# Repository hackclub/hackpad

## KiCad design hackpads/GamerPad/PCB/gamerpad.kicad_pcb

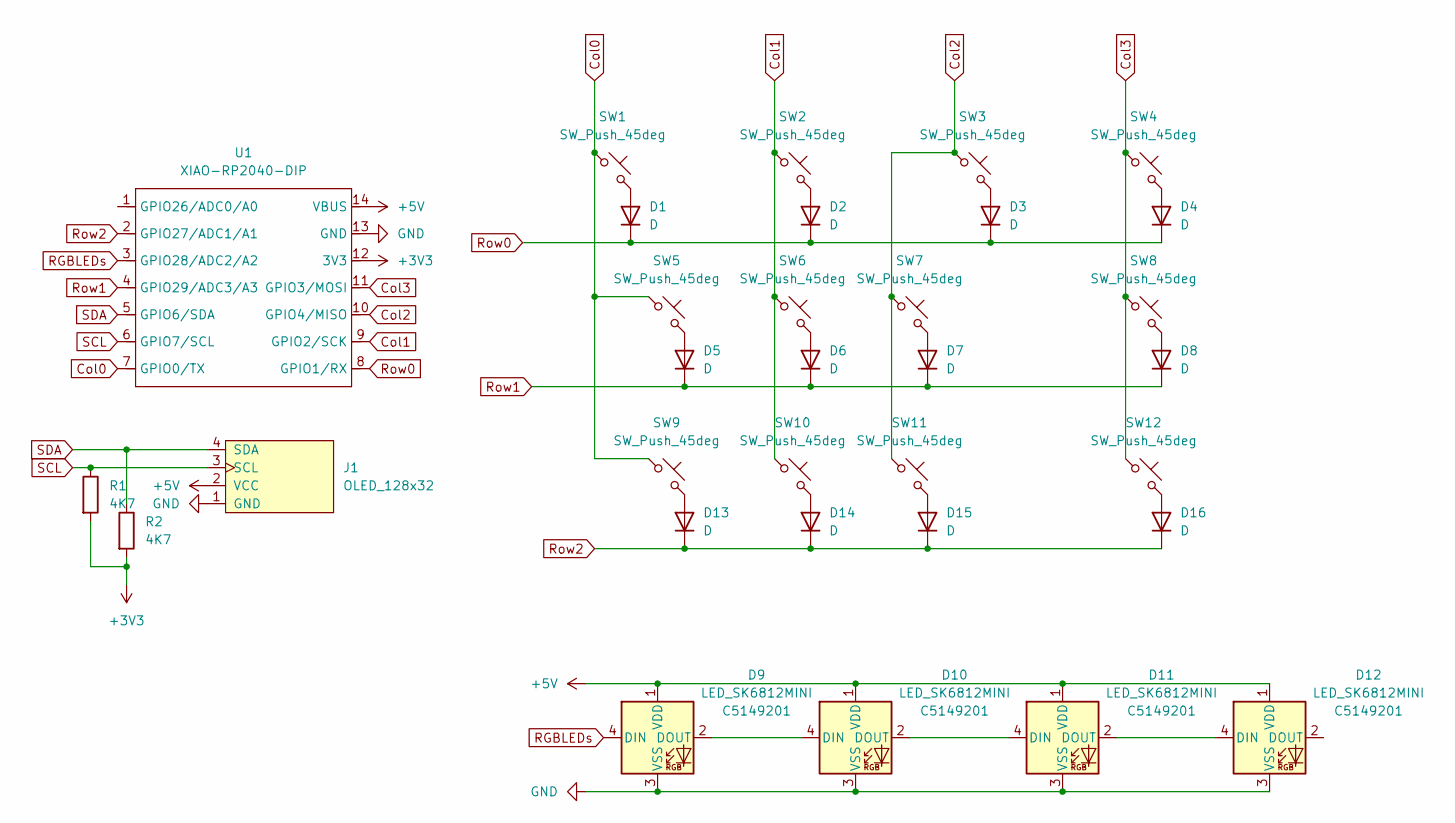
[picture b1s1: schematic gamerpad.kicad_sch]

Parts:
D1, D2, D3, D4, D5, D6, D7, D8, D13, D14, D15, D16: D; D_DO-35_SOD27_P7.62mm_Horizontal
D9, D10, D11, D12: LED_SK6812MINI; SK6812MINI-E; LCSC C5149201
J1: OLED_128x32
R1, R2: 4K7; R_Axial_DIN0204_L3.6mm_D1.6mm_P7.62mm_Horizontal
SW1, SW2, SW3, SW4, SW5, SW6, SW7, SW8, SW9, SW10, SW11, SW12: SW_Push_45deg; MX_PCB_1.00u
U1: XIAO-RP2040-DIP

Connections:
+3V3: R1.2, R2.2, U1.12 (3V3)
+5V: D9.1 (VDD), D10.1 (VDD), D11.1 (VDD), D12.1 (VDD), J1.2 (VCC), U1.14 (VBUS)
Col0: SW1.1, SW5.1, SW9.1, U1.7 (GPIO0/TX)
Col1: SW2.1, SW6.1, SW10.1, U1.9 (GPIO2/SCK)
Col2: SW3.1, SW7.1, SW11.1, U1.10 (GPIO4/MISO)
Col3: SW4.1, SW8.1, SW12.1, U1.11 (GPIO3/MOSI)
GND: D9.3 (VSS), D10.3 (VSS), D11.3 (VSS), D12.3 (VSS), J1.1 (GND), U1.13 (GND)
unnamed: D1.2 (A), SW1.2
unnamed: D2.2 (A), SW2.2
unnamed: D3.2 (A), SW3.2
unnamed: D4.2 (A), SW4.2
unnamed: D5.2 (A), SW5.2
unnamed: D6.2 (A), SW6.2
unnamed: D7.2 (A), SW7.2
unnamed: D8.2 (A), SW8.2
unnamed: D9.2 (DOUT), D10.4 (DIN)
unnamed: D10.2 (DOUT), D11.4 (DIN)
unnamed: D11.2 (DOUT), D12.4 (DIN)
unnamed: D13.2 (A), SW9.2
unnamed: D14.2 (A), SW10.2
unnamed: D15.2 (A), SW11.2
unnamed: D16.2 (A), SW12.2
RGBLEDs: D9.4 (DIN), U1.3 (GPIO28/ADC2/A2)
Row0: D1.1 (K), D2.1 (K), D3.1 (K), D4.1 (K), U1.8 (GPIO1/RX)
Row1: D5.1 (K), D6.1 (K), D7.1 (K), D8.1 (K), U1.4 (GPIO29/ADC3/A3)
Row2: D13.1 (K), D14.1 (K), D15.1 (K), D16.1 (K), U1.2 (GPIO27/ADC1/A1)
SCL: J1.3 (SCL), R1.1, U1.6 (GPIO7/SCL)
SDA: J1.4 (SDA), R2.1, U1.5 (GPIO6/SDA)

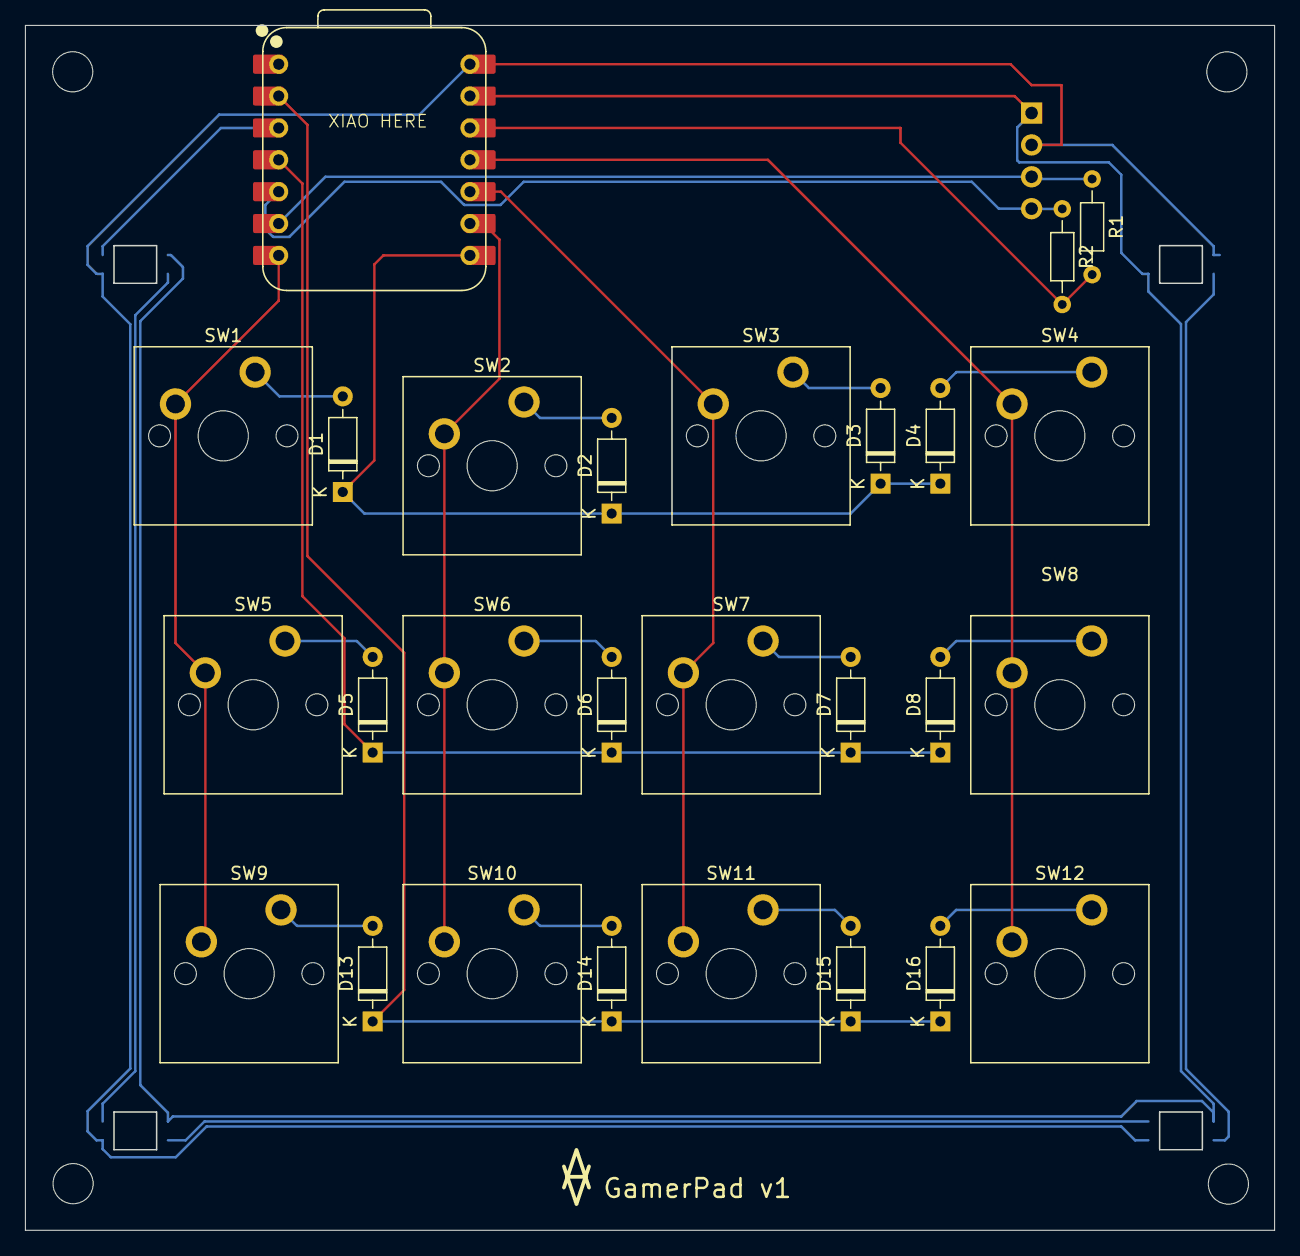
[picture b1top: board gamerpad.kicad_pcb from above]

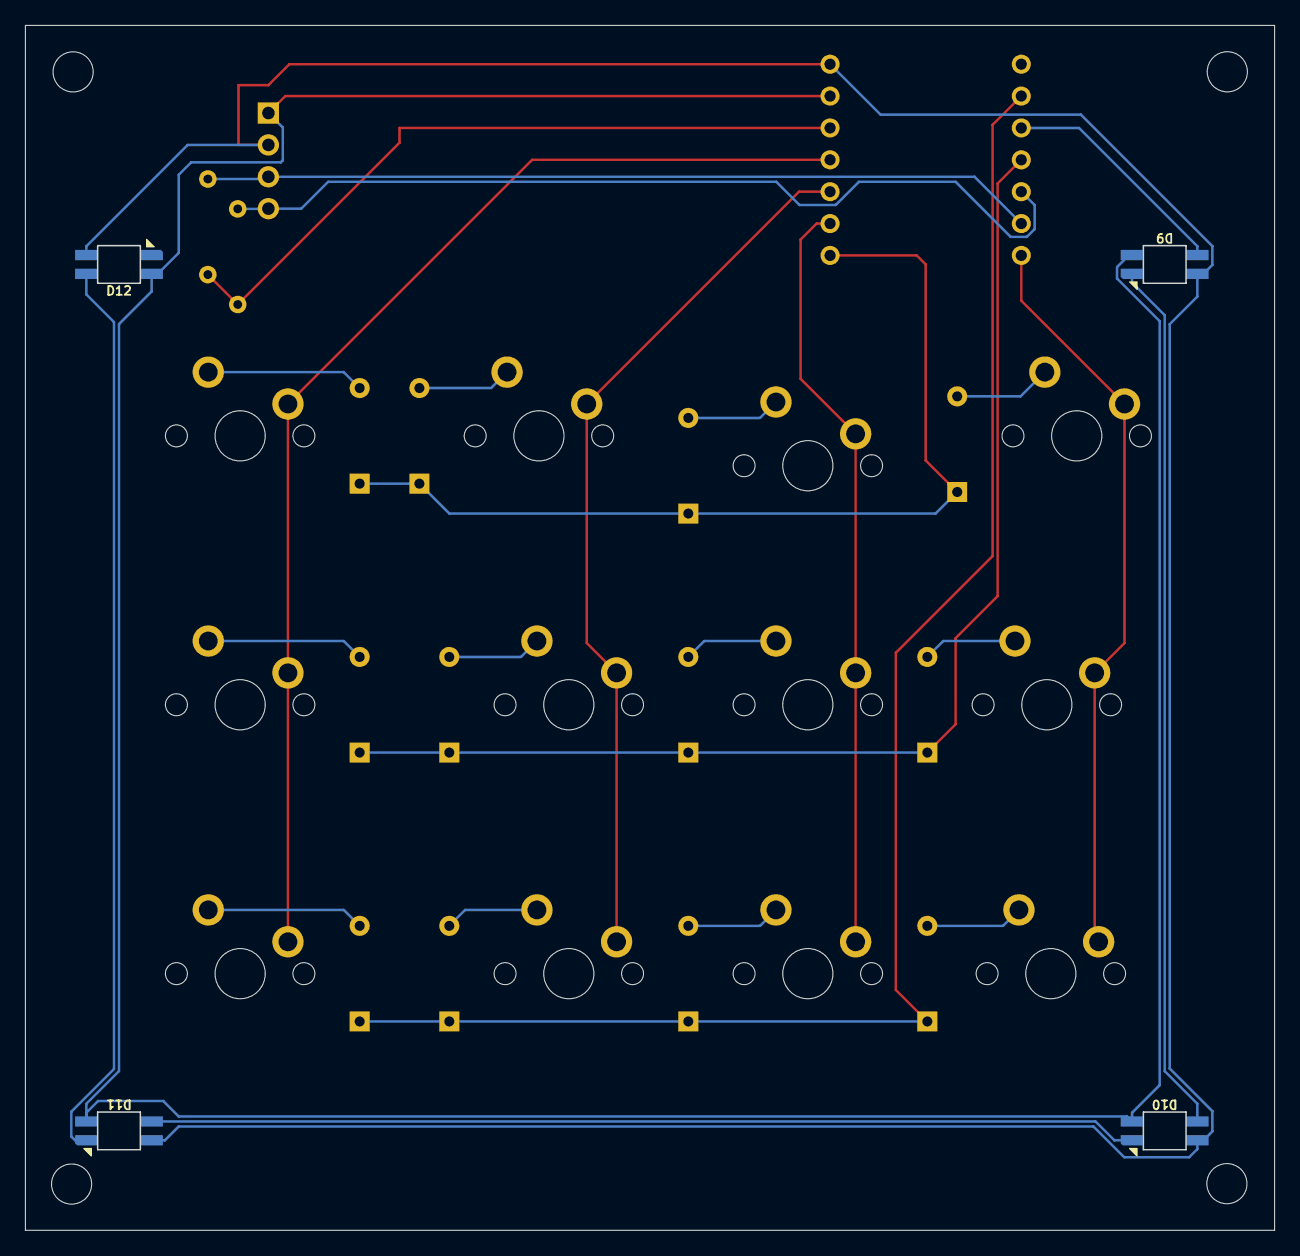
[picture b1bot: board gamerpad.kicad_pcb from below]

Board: 2 copper layers, 99.6 x 96.0 mm, 32 parts (4 on the bottom side), 28 nets.

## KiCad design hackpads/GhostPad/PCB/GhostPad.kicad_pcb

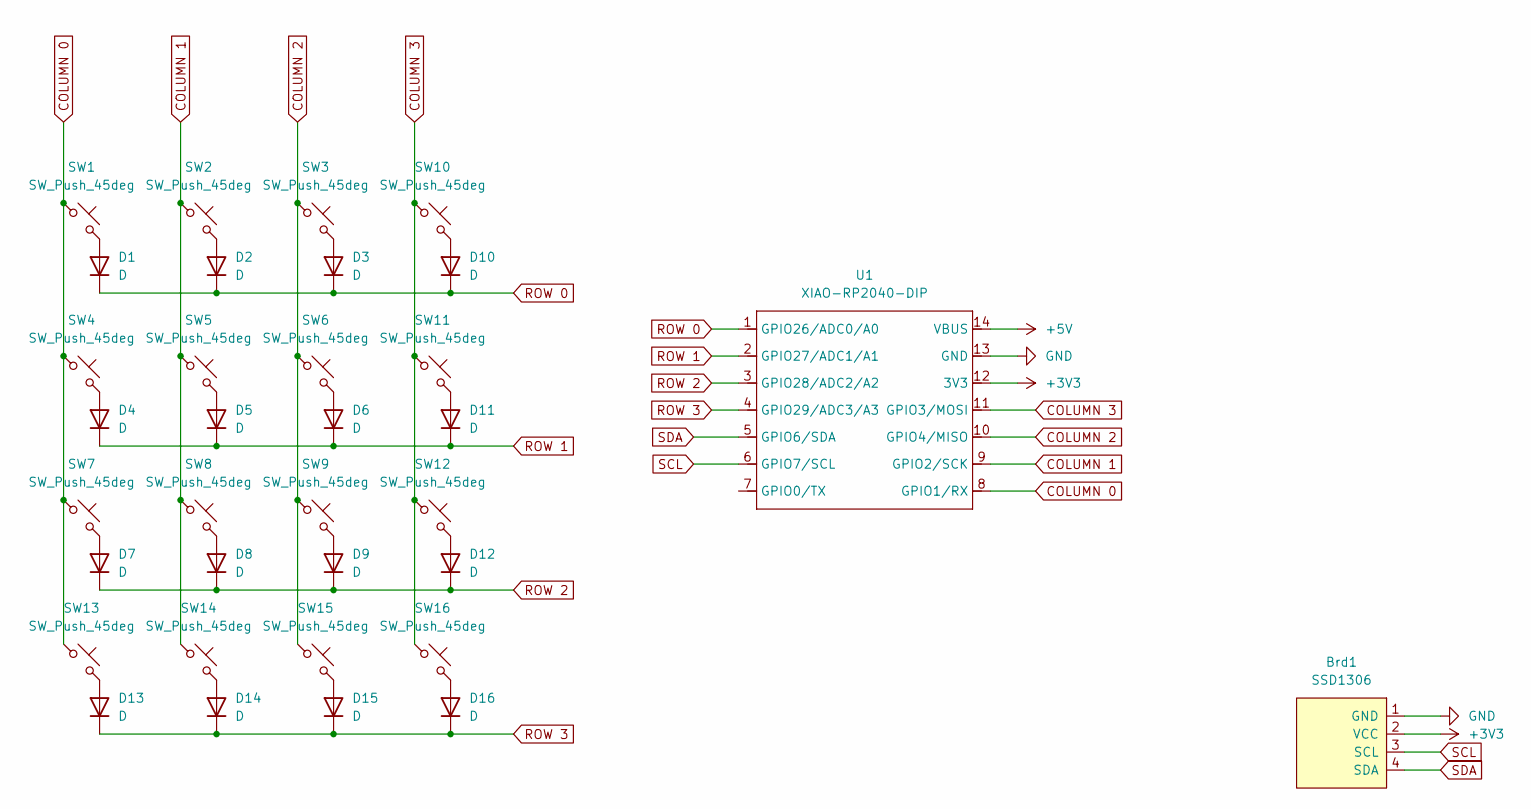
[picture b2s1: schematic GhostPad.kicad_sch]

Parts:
Brd1: SSD1306; 128x64OLED
D1, D2, D3, D4, D5, D6, D7, D8, D9, D10, D11, D12, D13, D14, D15, D16: D; D_0805_2012Metric_Pad1.15x1.40mm_HandSolder
SW1, SW2, SW3, SW4, SW5, SW6, SW7, SW8, SW9, SW10, SW11, SW12, SW13, SW14, SW15, SW16: SW_Push_45deg; SW_Cherry_MX_1.00u_PCB
U1: XIAO-RP2040-DIP

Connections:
+3V3: Brd1.2 (VCC), U1.12 (3V3)
+5V: U1.14 (VBUS)
COLUMN 0: SW1.1, SW4.1, SW7.1, SW13.1, U1.8 (GPIO1/RX)
COLUMN 1: SW2.1, SW5.1, SW8.1, SW14.1, U1.9 (GPIO2/SCK)
COLUMN 2: SW3.1, SW6.1, SW9.1, SW15.1, U1.10 (GPIO4/MISO)
COLUMN 3: SW10.1, SW11.1, SW12.1, SW16.1, U1.11 (GPIO3/MOSI)
GND: Brd1.1 (GND), U1.13 (GND)
unnamed: D1.2 (A), SW1.2
unnamed: D2.2 (A), SW2.2
unnamed: D3.2 (A), SW3.2
unnamed: D4.2 (A), SW4.2
unnamed: D5.2 (A), SW5.2
unnamed: D6.2 (A), SW6.2
unnamed: D7.2 (A), SW7.2
unnamed: D8.2 (A), SW8.2
unnamed: D9.2 (A), SW9.2
unnamed: D10.2 (A), SW10.2
unnamed: D11.2 (A), SW11.2
unnamed: D12.2 (A), SW12.2
unnamed: D13.2 (A), SW13.2
unnamed: D14.2 (A), SW14.2
unnamed: D15.2 (A), SW15.2
unnamed: D16.2 (A), SW16.2
ROW 0: D1.1 (K), D2.1 (K), D3.1 (K), D10.1 (K), U1.1 (GPIO26/ADC0/A0)
ROW 1: D4.1 (K), D5.1 (K), D6.1 (K), D11.1 (K), U1.2 (GPIO27/ADC1/A1)
ROW 2: D7.1 (K), D8.1 (K), D9.1 (K), D12.1 (K), U1.3 (GPIO28/ADC2/A2)
ROW 3: D13.1 (K), D14.1 (K), D15.1 (K), D16.1 (K), U1.4 (GPIO29/ADC3/A3)
SCL: Brd1.3 (SCL), U1.6 (GPIO7/SCL)
SDA: Brd1.4 (SDA), U1.5 (GPIO6/SDA)

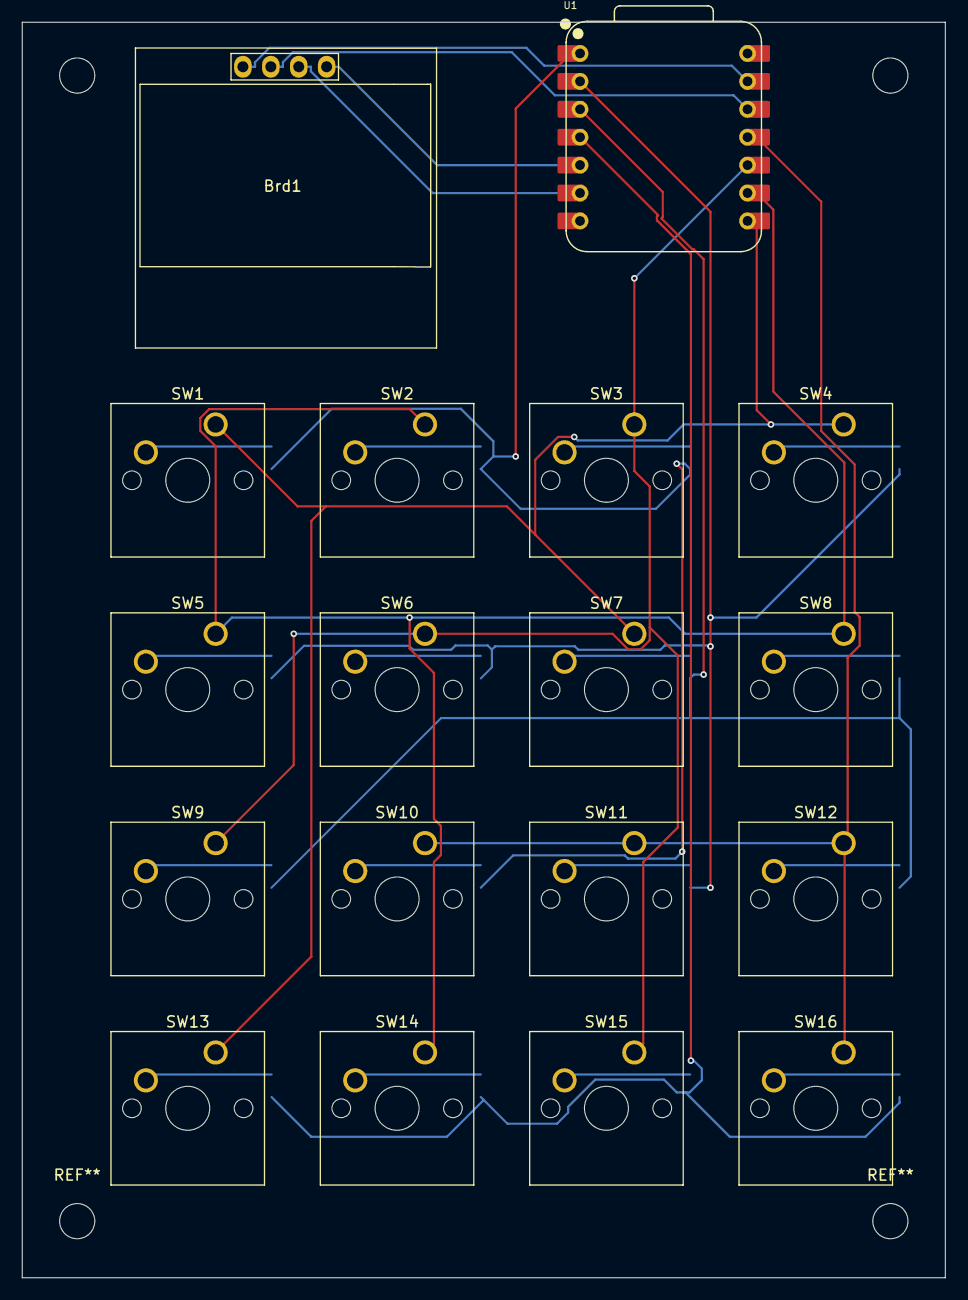
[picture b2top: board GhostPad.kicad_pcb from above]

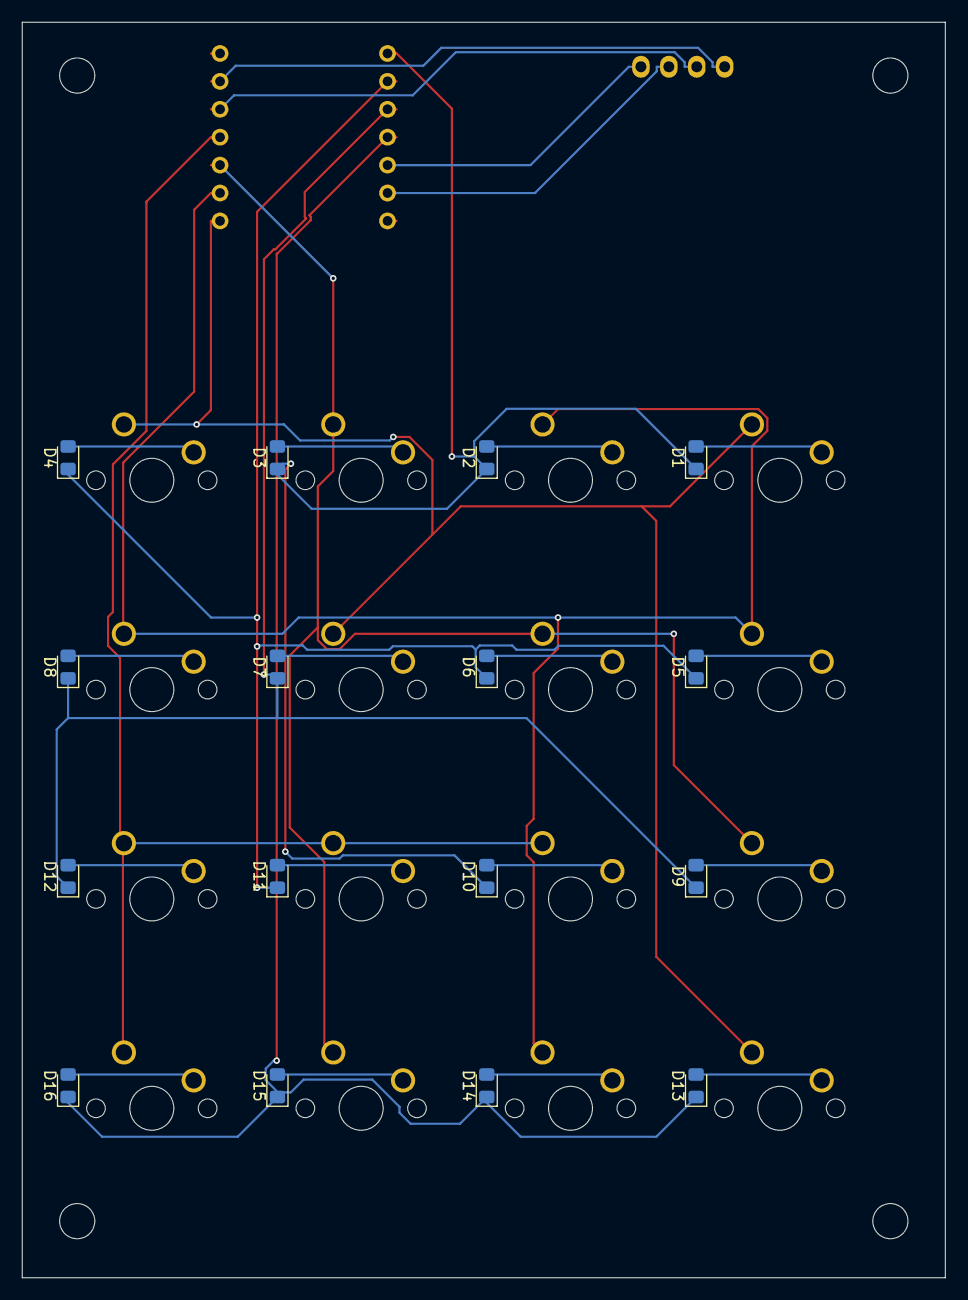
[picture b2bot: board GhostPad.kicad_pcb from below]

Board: 2 copper layers, 84.0 x 114.2 mm, 34 parts (16 on the bottom side), 28 nets.

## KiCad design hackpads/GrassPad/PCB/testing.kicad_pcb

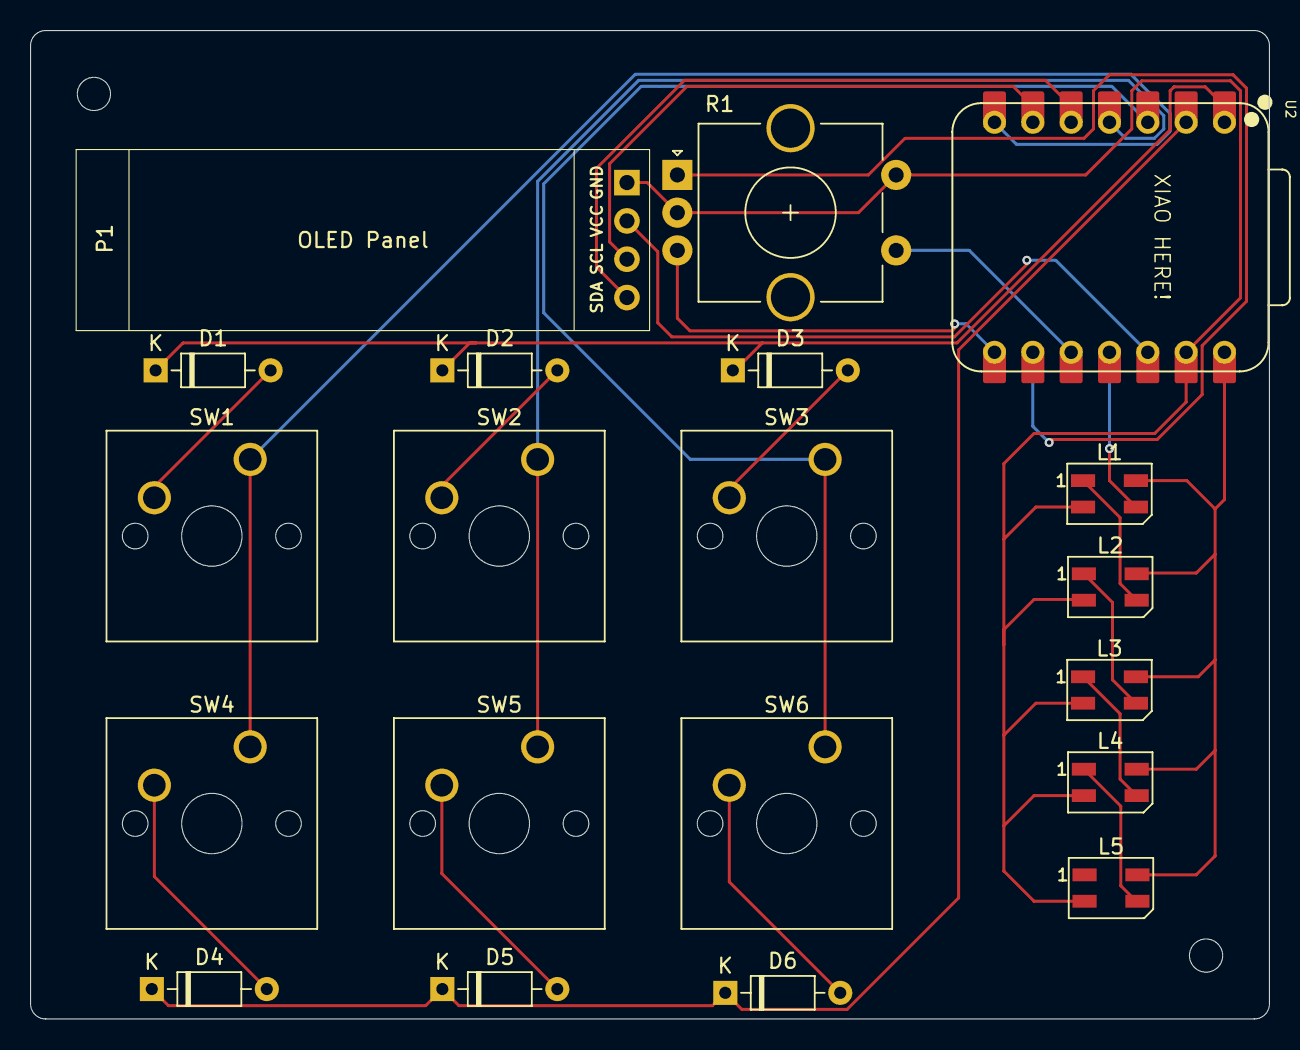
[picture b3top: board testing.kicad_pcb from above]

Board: 2 copper layers, 82.1 x 65.5 mm, 20 parts (0 on the bottom side), 24 nets.

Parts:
D1, D2, D3, D4, D5, D6: D; D_DO-35_SOD27_P7.62mm_Horizontal
L1, L2, L3, L4, L5: SK6812MINI; LED_SK6812MINI_PLCC4_3.5x3.5mm_P1.75mm
P1: Conn_01x04_Pin; SSD1306-0.91-OLED-4pin-128x32
R1: RotaryEncoder_Switch; RotaryEncoder_Alps_EC11E-Switch_Vertical_H20mm_CircularMoun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
SW1, SW2, SW3, SW4, SW5, SW6: SW_Push; SW_Cherry_MX_1.00u_PCB
U2: XIAO-RP2040-DIP

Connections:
+3.3V: P1.2, U2.12 (3V3)
+5V: L1.4 (VDD), L2.4 (VDD), L3.4 (VDD), L4.4 (VDD), L5.4 (VDD), U2.14 (VBUS)
GND: L1.2 (VSS), L2.2 (VSS), L3.2 (VSS), L4.2 (VSS), L5.2 (VSS), P1.1, R1.C, R1.S2, U2.13 (GND)
unnamed: L1.3 (DIN), U2.11 (GPIO3/MOSI)
unnamed: L1.1 (DOUT), L2.3 (DIN)
unnamed: L2.1 (DOUT), L3.3 (DIN)
unnamed: L3.1 (DOUT), L4.3 (DIN)
unnamed: L4.1 (DOUT), L5.3 (DIN)
unnamed: D1.2 (A), SW1.2
unnamed: D1.1 (K), D2.1 (K), D3.1 (K), U2.1 (GPIO26/ADC0/A0)
unnamed: D4.2 (A), SW4.2
unnamed: D4.1 (K), D5.1 (K), D6.1 (K), U2.2 (GPIO27/ADC1/A1)
unnamed: D5.2 (A), SW5.2
unnamed: D2.2 (A), SW2.2
unnamed: D3.2 (A), SW3.2
unnamed: D6.2 (A), SW6.2
unnamed: P1.3, U2.6 (GPIO7/SCL)
unnamed: P1.4, U2.5 (GPIO6/SDA)
unnamed: SW1.1, SW4.1, U2.7 (GPIO0/TX)
unnamed: R1.B, U2.8 (GPIO1/RX)
unnamed: R1.A, U2.9 (GPIO2/SCK)
unnamed: R1.S1, U2.10 (GPIO4/MISO)
unnamed: SW3.1, SW6.1, U2.3 (GPIO28/ADC2/A2)
unnamed: SW2.1, SW5.1, U2.4 (GPIO29/ADC3/A3)

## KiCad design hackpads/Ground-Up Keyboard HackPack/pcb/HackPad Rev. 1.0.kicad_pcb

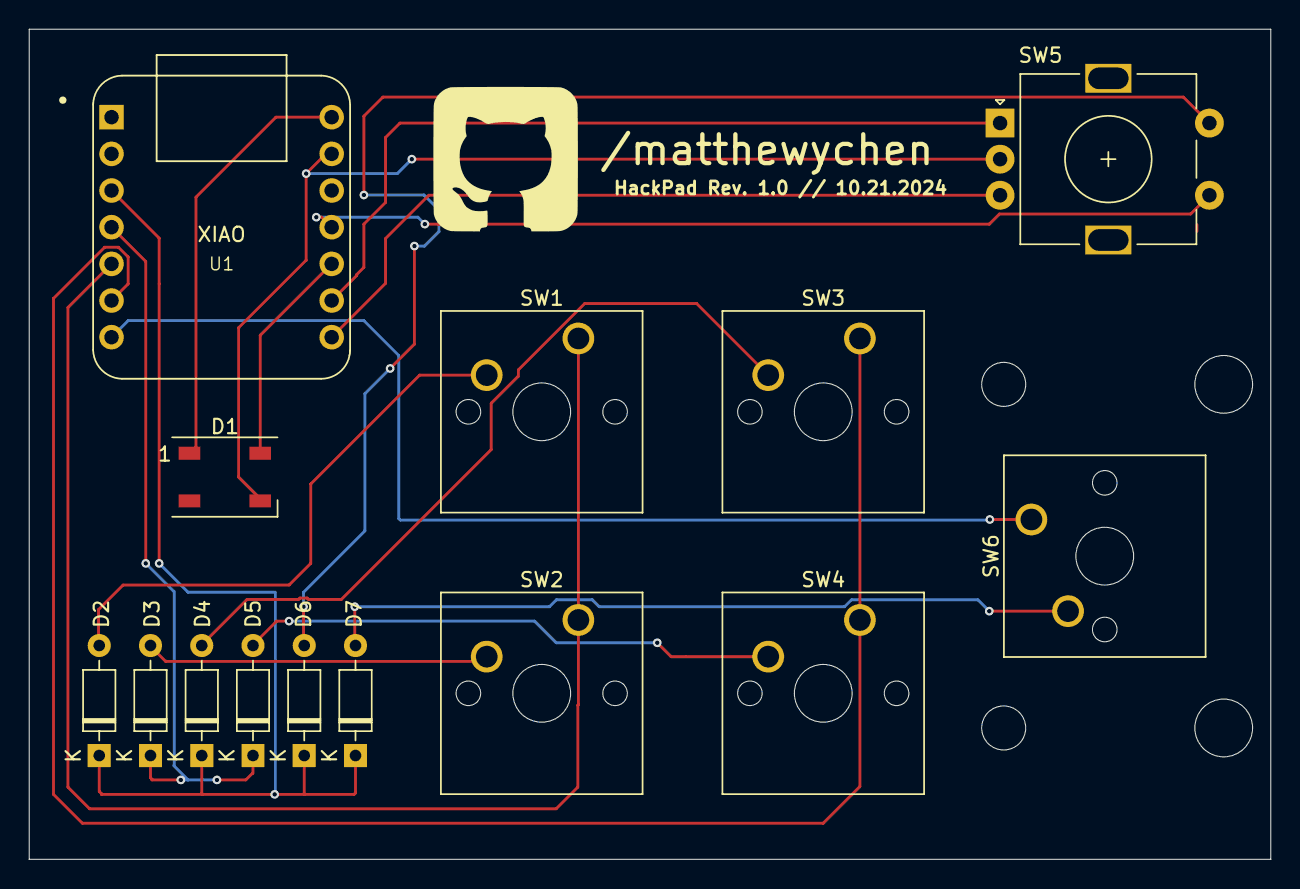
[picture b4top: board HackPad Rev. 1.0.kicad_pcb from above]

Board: 2 copper layers, 86.0 x 57.5 mm, 14 parts (0 on the bottom side), 17 nets.

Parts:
D1: WS2812B; LED_WS2812B_PLCC4_5.0x5.0mm_P3.2mm
D2, D3, D4, D5, D6, D7: D; D_DO-35_SOD27_P7.62mm_Horizontal
SW1, SW2, SW3, SW4: SW_Push_45deg; SW_Cherry_MX_1.00u_PCB
SW5: RotaryEncoder_Switch; RotaryEncoder_Alps_EC11E-Switch_Vertical_H20mm
SW6: SW_Push_45deg; SW_Cherry_MX_2.00u_PCB
U1: Seeed Studio XIAO SAMD21; XIAO-Generic-Thruhole-14P-2.54-21X17.8MM

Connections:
/C0: SW1.1, SW2.1, U1.5 (PA8_A4_D4_SDA)
/C2: SW3.1, SW4.1, U1.6 (PA9_A5_D5_SCL)
/C3: SW5.S1, U1.11 (PA6_A10_D10_MOSI)
GND: D1.3 (VSS), SW5.C, U1.13 (GND)
unnamed: D1.4 (DIN), U1.10 (PA5_A9_D9_MISO)
unnamed: D2.2 (A), SW1.2
unnamed: D2.1 (K), D4.1 (K), D6.1 (K), D7.1 (K), U1.3 (PA10_A2_D2)
unnamed: D3.2 (A), SW2.2
unnamed: D3.1 (K), D5.1 (K), U1.4 (PA11_A3_D3)
unnamed: D4.2 (A), SW3.2
unnamed: D5.2 (A), SW4.2
unnamed: D6.2 (A), SW5.S2
unnamed: D7.2 (A), SW6.2
unnamed: SW5.A, U1.9 (PA7_A8_D8_SCK)
unnamed: SW6.1, U1.7 (PB08_A6_D6_TX)
unnamed: SW5.B, U1.8 (PB09_A7_D7_RX)
VCC: D1.1 (VDD), U1.14 (5V)

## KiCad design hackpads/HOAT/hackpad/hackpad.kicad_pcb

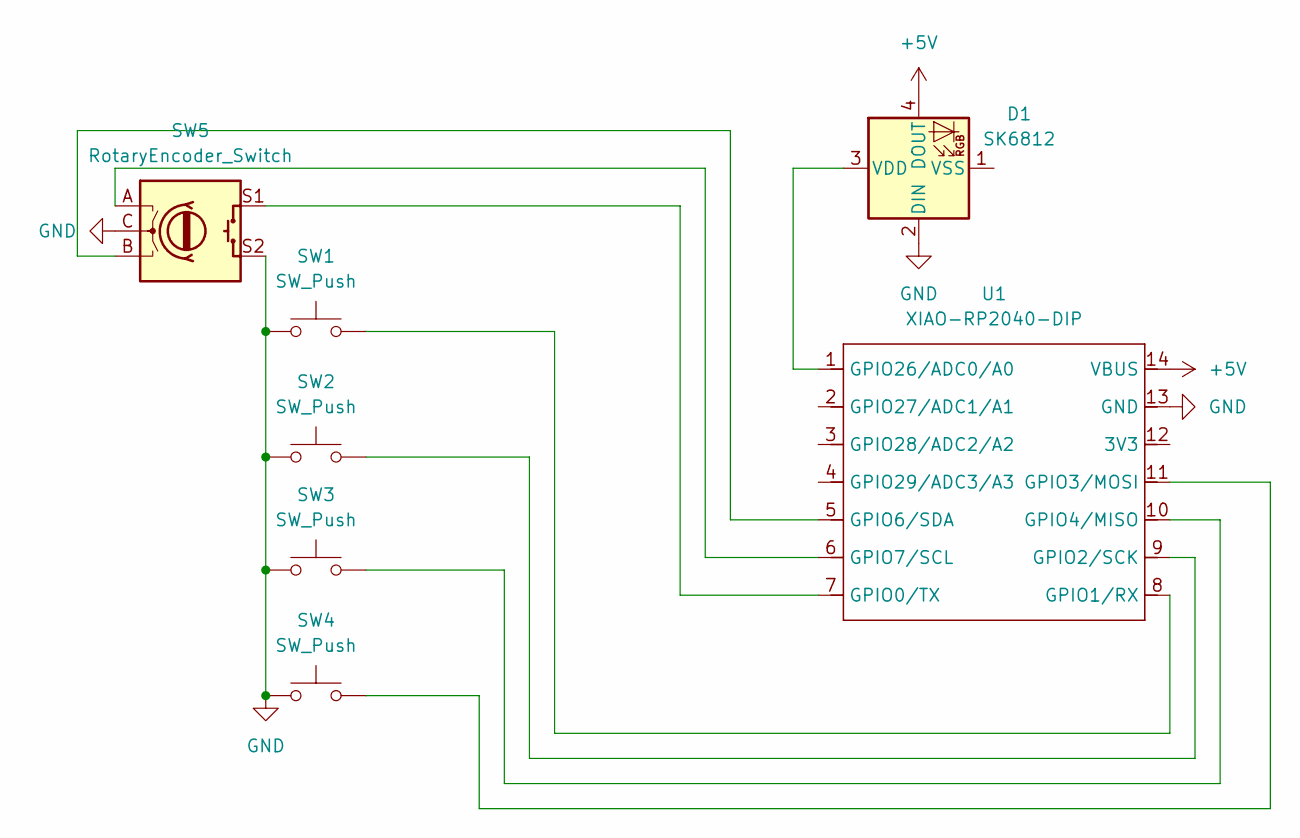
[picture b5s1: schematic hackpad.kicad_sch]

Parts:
D1: SK6812; LED_SK6812_PLCC4_5.0x5.0mm_P3.2mm
SW1, SW2, SW3, SW4: SW_Push; SW_Cherry_MX_1.00u_PCB
SW5: RotaryEncoder_Switch; RotaryEncoder_Alps_EC11E-Switch_Vertical_H20mm
U1: XIAO-RP2040-DIP

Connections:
+5V: D1.4 (DOUT), U1.14 (VBUS)
GND: D1.2 (DIN), SW1.1, SW2.1, SW3.1, SW4.1, SW5.C, SW5.S2, U1.13 (GND)
unnamed: D1.3 (VDD), U1.1 (GPIO26/ADC0/A0)
unnamed: SW5.S1, U1.7 (GPIO0/TX)
unnamed: SW1.2, U1.8 (GPIO1/RX)
unnamed: SW2.2, U1.9 (GPIO2/SCK)
unnamed: SW4.2, U1.11 (GPIO3/MOSI)
unnamed: SW3.2, U1.10 (GPIO4/MISO)
unnamed: SW5.B, U1.5 (GPIO6/SDA)
unnamed: SW5.A, U1.6 (GPIO7/SCL)

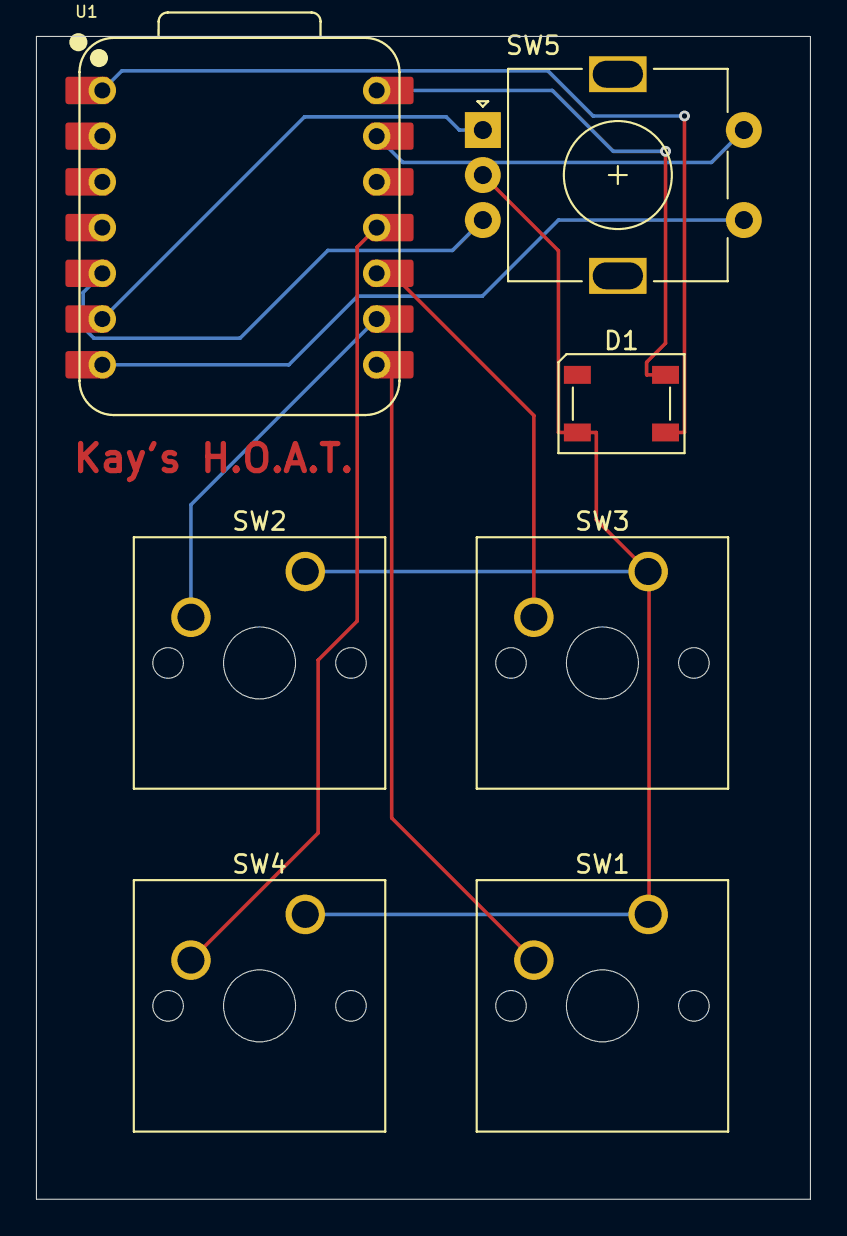
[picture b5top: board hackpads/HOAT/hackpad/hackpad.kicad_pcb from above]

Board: 2 copper layers, 43.0 x 64.6 mm, 7 parts (0 on the bottom side), 10 nets.

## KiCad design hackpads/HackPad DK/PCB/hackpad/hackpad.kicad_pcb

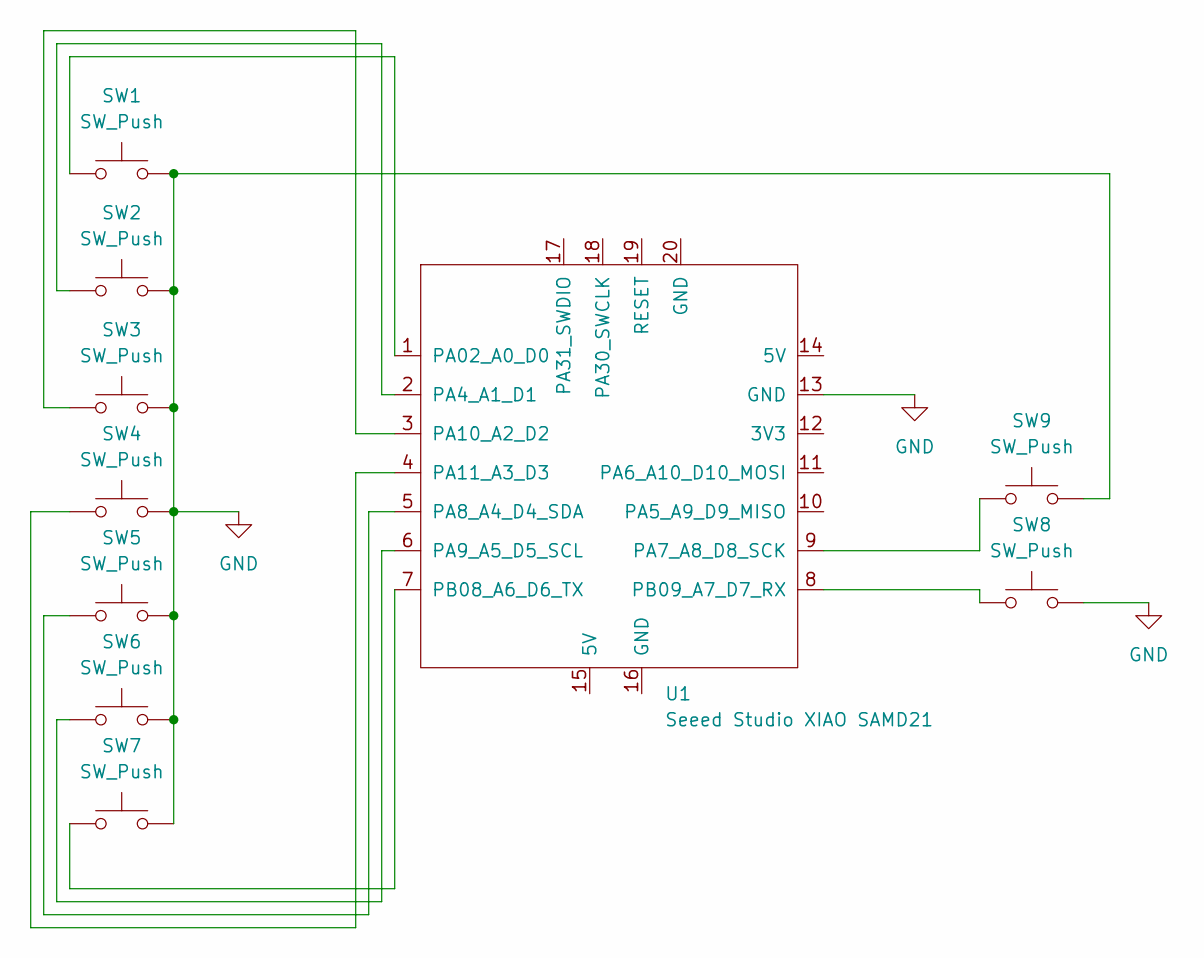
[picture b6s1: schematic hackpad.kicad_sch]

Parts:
SW1, SW2, SW3, SW4, SW5, SW6, SW7, SW8, SW9: SW_Push; SW_Cherry_MX_1.00u_PCB
U1: Seeed Studio XIAO SAMD21; XIAO-Generic-Thruhole-14P-2.54-21X17.8MM

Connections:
GND: SW1.2, SW2.2, SW3.2, SW4.2, SW5.2, SW6.2, SW7.2, SW8.2, SW9.2, U1.13 (GND)
unnamed: SW1.1, U1.1 (PA02_A0_D0)
unnamed: SW2.1, U1.2 (PA4_A1_D1)
unnamed: SW9.1, U1.9 (PA7_A8_D8_SCK)
unnamed: SW5.1, U1.5 (PA8_A4_D4_SDA)
unnamed: SW6.1, U1.6 (PA9_A5_D5_SCL)
unnamed: SW3.1, U1.3 (PA10_A2_D2)
unnamed: SW4.1, U1.4 (PA11_A3_D3)
unnamed: SW7.1, U1.7 (PB08_A6_D6_TX)
unnamed: SW8.1, U1.8 (PB09_A7_D7_RX)

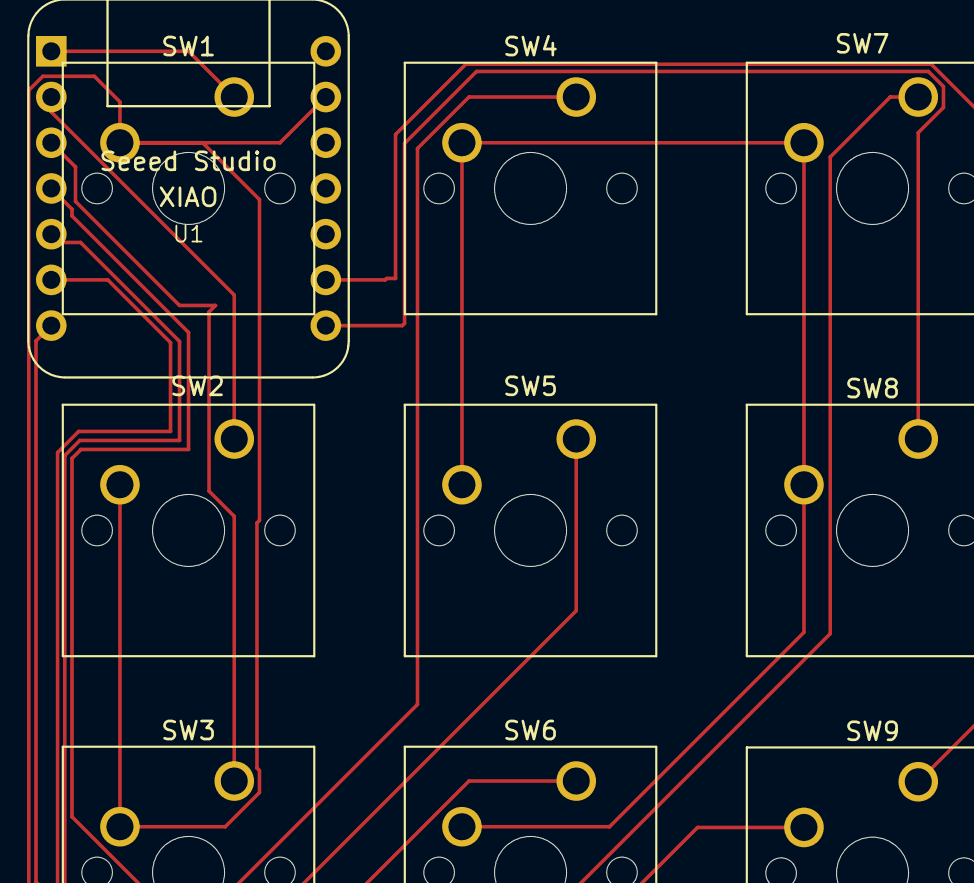
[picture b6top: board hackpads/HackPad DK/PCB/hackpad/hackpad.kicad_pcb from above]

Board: 2 copper layers, 10 parts (0 on the bottom side), 10 nets.
